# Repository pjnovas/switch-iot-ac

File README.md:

# Switch IoT [AC]

This is a simple switch, just a push button to send a MQTT message. The idea behind it is to create an automation in HASSIO using the MQTT message as a trigger.  

My current prototype testing case is to toggle a Wiz Light Bulb.

----

# How to

1. Set up `config.example` into `config.h` with your settings.
2. Upload the code into an ESP-01

It will use the `BUILTIN_LED` to show the status:

- When connecting to wifi will stay on
- When trigger message will stay on while sending the MQTT message

Schema:

---

Currently I'm building my prototype PCBs so I leave here all the `KiCad` files

---

ROADMAP: Move config.h settings into EEPROM and create wifi network by long-pressing to configure EEPROM

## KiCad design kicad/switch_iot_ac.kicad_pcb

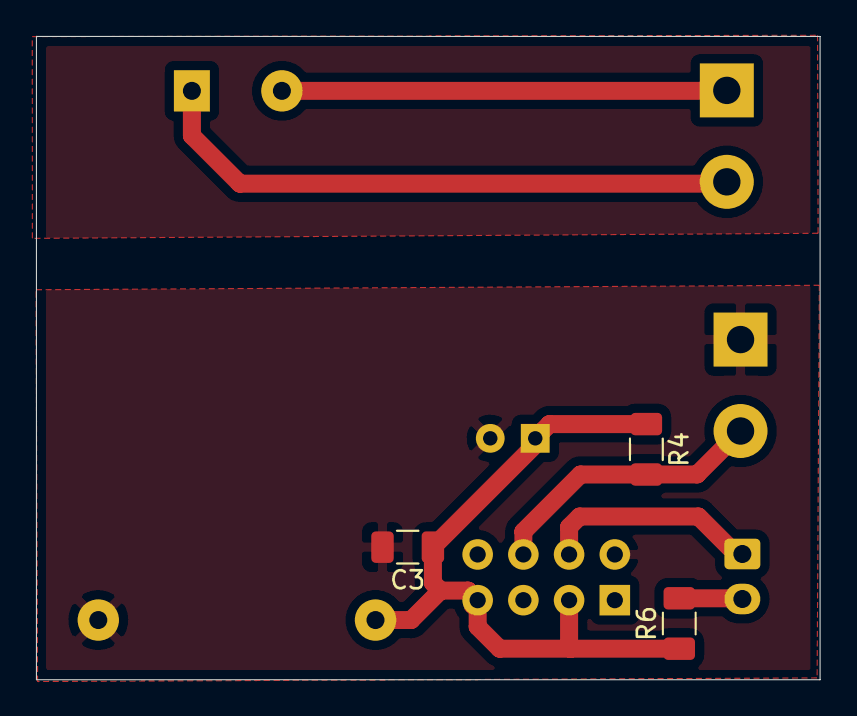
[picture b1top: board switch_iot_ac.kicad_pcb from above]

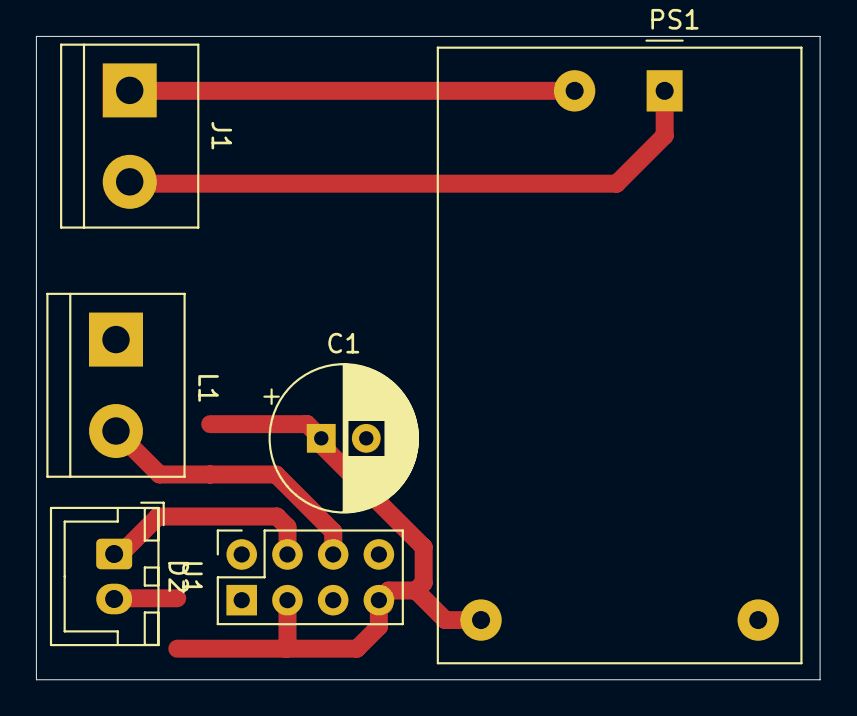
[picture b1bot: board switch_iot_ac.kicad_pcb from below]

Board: 2 copper layers, 43.5 x 35.7 mm, 9 parts (6 on the bottom side), 7 nets.

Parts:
C1: 100uf; CP_Radial_D8.0mm_P2.50mm
C3: 100nf; C_1206_3216Metric
D2: LED; JST_XH_B2B-XH-A_1x02_P2.50mm_Vertical
J1: AC IN; TerminalBlock_bornier-2_P5.08mm
L1: SwitchSignal; TerminalBlock_bornier-2_P5.08mm
PS1: HLK-PM01; Converter_ACDC_HiLink_HLK-PMxx
R4: 1k; R_1206_3216Metric
R6: 220; R_1206_3216Metric
U1: ESP-01v090; PinSocket_2x04_P2.54mm_Vertical

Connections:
/NOTIFY: D2.1, U1.4
/PWR_IN: C1.1, C3.1, PS1.4, R4.1, R6.1, U1.3, U1.7
/TRIGGER: L1.2, R4.2, U1.6
GND: C1.2, C3.2, L1.1, PS1.3, U1.2
unnamed: D2.2, R6.2
unnamed: J1.1, PS1.2
unnamed: J1.2, PS1.1
